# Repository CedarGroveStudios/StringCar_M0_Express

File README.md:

# StringCar_M0_Express

A Circuit-Python compatible string car racer controller board.

The Cedar Grove StringCar M0 Express is an ATSAMD21-based CircuitPython compatible board used to control a simple string car racer robot. The board is architecturally similar to the Adafruit Trinket M0 and ItsyBitsy M0 Express microcontroller boards with the addition of battery management and a DC motor controller. This board features JST connectors for the racer's battery, motor output, and sensor input. LiPo battery management charge rate is 500mA. For sensor experimentation, a 3.3-volt Stemma-QT connection is available on-board. The micro-USB connector is used for REPL operation, operational status data output, and battery charging. On-board flash memory size is 2MB.

The StringCar M0 Express board will not be sold. The GitHub repository will contain design files and links for the BOM and to the shared OSH Park project.

The string car racer is a simple one-motor robot that is suspended from a string using a pulley attached to the motor shaft. Its challenge is to race back and forth from one end of a taut string to the other. The fastest car wins. The controller board uses sensor switches to detect the ends of the string, calculate the string length, then control motor speed and braking to avoid string-end collisions.

The objective is to create a string car racer that can autonomously learn about its environment and adjust tradeoffs for speed and battery longevity. CircuitPython is used to easily add and interactively adjust performance features such as motor and battery efficiency, end-of-string collision avoidance, string length calculation, and predictive braking. Also, being able to watch its own battery status means that it'll always return to the home end of the string when battery capacity begins to wane. Circuit Python also supports libraries that abstract string car functions, simplifying the primary code module to make it easier for novice programmers to get involved in customizing  string car racer operation.

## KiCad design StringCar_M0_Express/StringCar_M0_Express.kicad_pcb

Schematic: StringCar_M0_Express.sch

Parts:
BZ1: PKMCS0909E4000-R1; Piezo_9x9mm_PKMCS0909E4000-R1; MPN PKMCS0909E4000-R1; Digi-Key_PN 490-9647-1-ND
C1, C5: 1uF; C_0805
C2: 0.1uF; C_0805
C3, C6, C7: 10uF; C_0805
C4: 220uF; CP_Elect_6.6x6.6
C8: 0.01uF; C_0805
D1: MM3Z3V6T1G; D_SOD-323
D2: MBR120; D_SOD-123F
D3: SMAJ6.0A; D_SMA
J1: USB_MICRO; USB_Micro-B_Molex-105017-0001
J2: SENSOR_IN; JST_SH_SM02B-SRSS-TB_02x1.00mm_Angled
J3: SWD; Pin_Header_Straight_2x05_Pitch1.27mm_SMD
J4: STEMMA-QT; JST_SH_SM04B-SRSS-TB_04x1.00mm_Angled
J5: MOTOR; JST_PH_S2B-PH-SM4-TB_02x2.00mm_Angled
J6: LIPO_BATT; JST_PH_S2B-PH-SM4-TB_02x2.00mm_Angled
LED1: RED; LED_0805
LED2: APA102_DOTSTAR; LED_RGB_5050-6
LED3: ORG; LED_0805
Q1, Q2: DMG2305UX-13; SOT-23-3; MPN DMG2305UX-13; Digi-Key_PN DMG2305UX-13DICT-ND
R1: 1.5K; R_0805
R2: 10K; R_0805
R3: 1K; R_0805
R4, R6, R9, R10: 100K; R_0805
R5: 4.7K; R_0805
R8: 2K; R_0805
SW1: RESET; TL3330AF_SPST_BUTTON_RT-ANGLE_7.8mm_2.5mm_2.5mm
SW2: POWER; SW_SPDT_CK-JS102011SAQN
U1: SAMD21E18A; TQFP-32_7x7mm_Pitch0.8mm
U2: AT25SF161; SOIC-8_W3.9mm
U3: DRV8833PWPR; TSSOP-16-1EP_W4.40mm; MPN DRV8833PWPR; Digi-Key_PN 296-29434-1-ND
U4: MCP73831-2-OT; SOT-23-5
U5: AP2112-3.3; SOT-23-5_HandSoldering

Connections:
+3V3: C5.1, C6.1, J3.1, J4.2, LED2.4, R2.1, U1.9, U1.30, U2.3 (~WP), U2.7 (~HOLD), U2.8 (Vcc), U3.1, U5.5
/DOTSTAR_CI: LED2.2, U1.2
/DOTSTAR_DI: LED2.1, U1.1
/FLASHMISO: U1.20, U2.2 (MISO)
/FLASHMOSI: U1.17, U2.5 (MOSI)
/FLASHSCK: U1.18, U2.6 (SCK)
/FLASH_CS: R2.2, U1.14, U2.1 (~CS)
/LED_STATUS: R1.2, U1.13
/MOTOR_OUT_1: U1.7, U3.9, U3.16
/MOTOR_OUT_2: U1.8, U3.10, U3.15
/PIEZO: BZ1.1, U1.11
/SCL: J4.4, U1.6
/SDA: J4.3, U1.5
/SENSOR_IN: R5.2, U1.12
/SWCLK: J3.4, U1.31
/SWDIO: J3.2, U1.32
/USB_D+: J1.3, U1.24
/USB_D-: J1.2, U1.23
/V+: C2.1, C4.1, C8.1, Q2.3, R4.2, R6.2, U3.12, U5.1
/VBAT: C7.1, J6.1, Q1.3, U4.3 (Vbat)
/VBUS: D2.2, D3.1, J1.1, LED3.2, Q1.1, R10.2, U4.4 (Vdd)
/VOLTAGE_MONITOR: R6.1, R9.2, U1.3
/Vbus: D2.1, Q1.2, Q2.2, SW2.1
/~RESET: J3.10, SW1.2, U1.26
GND: BZ1.2, C1.2, C3.1, C4.2, C5.2, C6.2, C7.2, C8.2, D1.2, D3.2, J1.5, J1.6, J2.2, J3.3, J3.5, J3.7, J3.9, J4.1, J6.2, LED1.1, LED2.3, R8.1, R9.1, R10.1, SW1.1, SW2.3, U1.10, U1.28, U2.4 (GND), U3.3, U3.6, U3.13, U3.17, U4.2 (Vss), U5.2
unnamed: C1.1, U1.29
unnamed: C2.2, U3.11
unnamed: C3.2, U3.14
unnamed: D1.1, J2.1, R5.1
unnamed: J5.1, U3.2, U3.7
unnamed: J5.2, U3.4, U3.5
unnamed: LED1.2, R1.1
unnamed: LED3.1, R3.2
unnamed: Q2.1, SW2.2
unnamed: R3.1, U4.1 (STAT)
unnamed: R4.1, U5.3
unnamed: R8.2, U4.5 (PROG)

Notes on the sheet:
Power Management
Internal SPI on SERCOM2
2MB (16Mbit) Flash
CHARGE
500mA CHARGE RATE
Battery Management
Motor Control
Serial Wire Debug Port
Battery Voltage Monitor (A0)
D13 LED
WARNING: The stock schematic symbol for the DMG2305UX-13 provided by DigiKey incorrectly swapped source and drain. The corrected symbol is shown here.

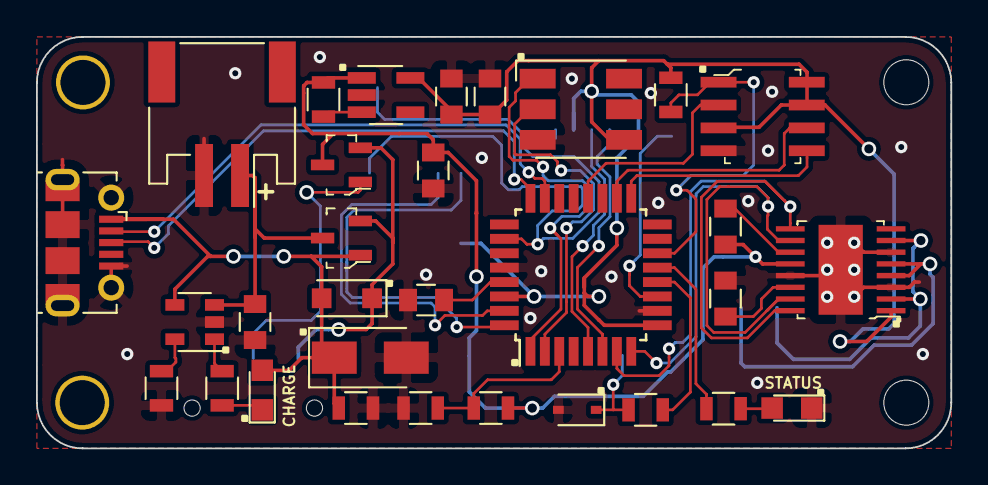
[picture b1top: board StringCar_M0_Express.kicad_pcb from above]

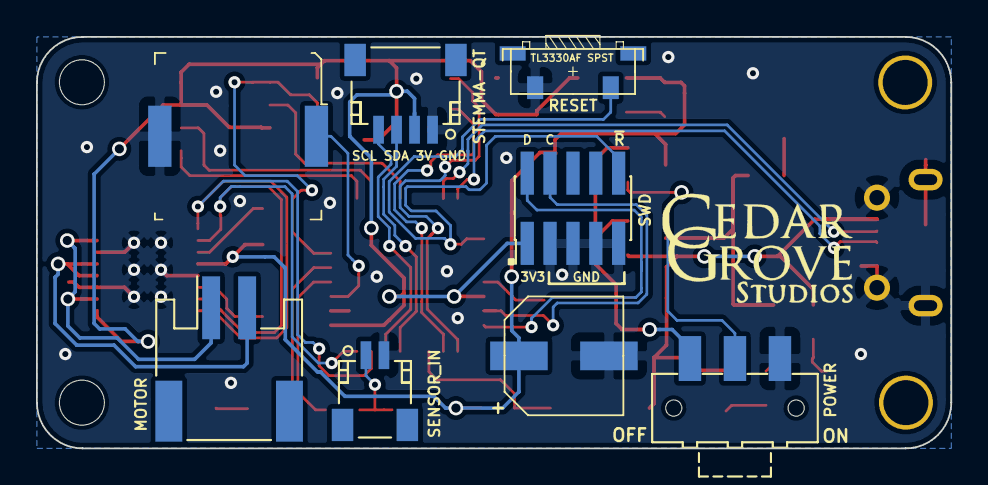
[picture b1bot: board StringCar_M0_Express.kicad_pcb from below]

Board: 2 copper layers, 50.8 x 22.9 mm, 39 parts (8 on the bottom side), 37 nets.

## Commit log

2019-10-17 initial repo load
2019-10-17 remove lengthy videos
2019-10-17 remove large composite photo file
2019-10-17 replace .pdf version of guides with URL
2019-10-17 update folder names
2019-10-21 update pcb layout and logo graphics
2019-10-21 update board layout and graphics
2019-10-21 updated logos and graphics
2019-11-17 update footprints
2019-12-22 update board layout graphic
2020-01-18 repair schematic and regenerate PCB as v05
2020-01-18 fix schematic and update PCB to v05
2020-01-18 update schematic with symbol correction; add warning
2020-07-31 correct stemma-qt pinout
2020-08-07 update PCB
2020-09-01 update schematic
2020-09-04 Update schematic and test code
2020-09-05 add boomerpong source code and references
2020-09-06 remove debug lines
2020-09-07 update motor PWM frequency in library
2020-12-14 update to an improved PWM frequency
2021-03-04 update graphics
2021-03-04 update graphics; remove graphics archive
2021-03-06 update motor specs; change driver to braking mode
2021-04-13 update PCB solder paste clearance
2021-07-12 update documentation
2021-08-05 Update fp-info-cache
2022-09-02 update license
2022-12-15 update docs
2023-02-18 reorganize
